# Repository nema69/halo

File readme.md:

# Light Module

## Anforderungen

- Ring mit OD = 50mm und ID = 15mm

- Strom max. 500 mA

- Nennspannung = 24V

## LEDs

#### HONGLITRONIC A2835W6H2-D01-8D2AB5

- LCSC: [C7423447]([A2835W6H2-D01-8D2AB5 HONGLITRONIC(Hongli Zhihui (HONGLITRONIC)) | Optoelectronics - LCSC Electronics](https://www.lcsc.com/product-detail/LED-Indication-Discrete_HONGLITRONIC-Hongli-Zhihui-HONGLITRONIC-A2835W6H2-D01-8D2AB5_C7423447.html))

- Package: SMD2835

- Farbe: Kaltweiß (6500K)

- 

## TODO:

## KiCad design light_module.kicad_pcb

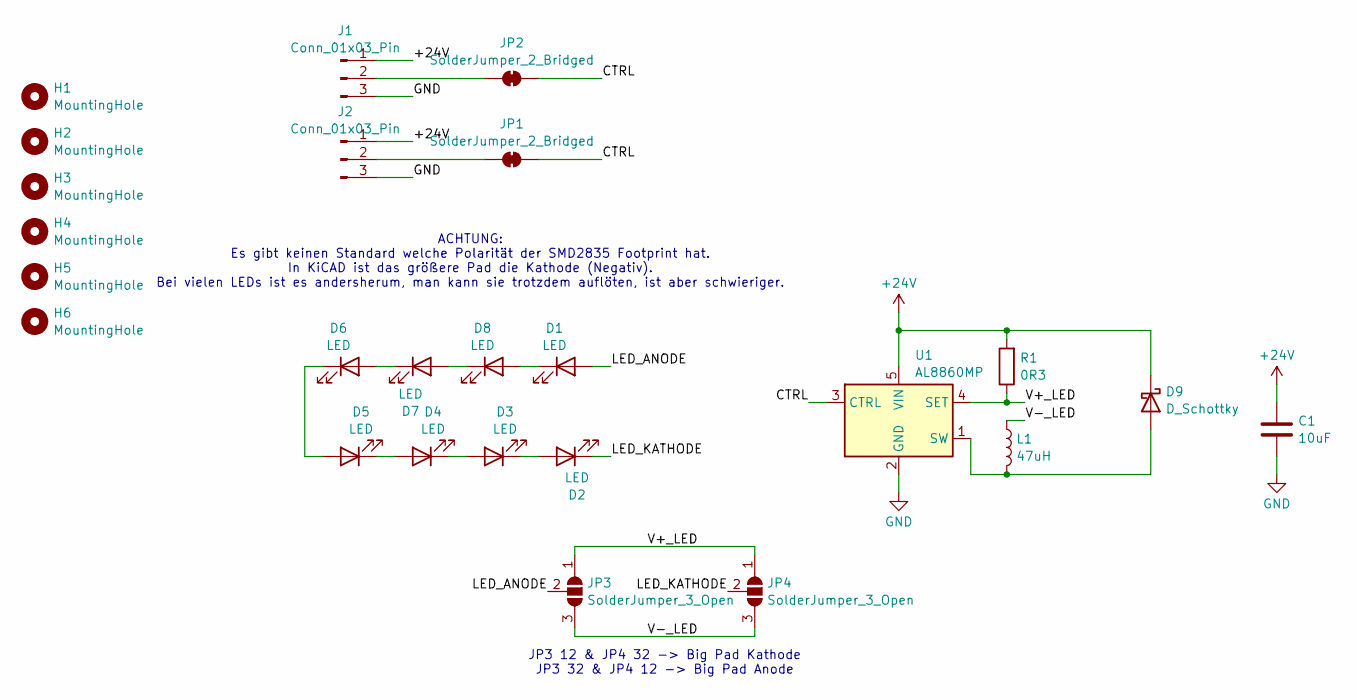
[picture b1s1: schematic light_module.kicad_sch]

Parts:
C1: 10uF; C_1206_3216Metric_Pad1.33x1.80mm_HandSolder; JLC PN C13585
D1, D2, D3, D4, D5, D6, D7, D8: LED; LED_PLCC_2835_Handsoldering; JLC PN C385302
D9: D_Schottky; D_SOD-123; JLC PN C78545
H1, H2, H3, H4, H5, H6: MountingHole; MountingHole_3.2mm_M3
J1, J2: Conn_01x03_Pin; JST_XH_B3B-XH-A_1x03_P2.50mm_Vertical
JP1, JP2: SolderJumper_2_Bridged; SolderJumper-2_P1.3mm_Bridged_RoundedPad1.0x1.5mm
JP3, JP4: SolderJumper_3_Open; SolderJumper-3_P1.3mm_Open_RoundedPad1.0x1.5mm_NumberLabels
L1: 47uH; L_Changjiang_FNR5020S; JLC PN C5363775
R1: 0R3; R_0805_2012Metric; JLC PN C247157
U1: AL8860MP; TSOT-23-5; JLC PN C155534

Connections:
+24V: C1.1, D9.1 (K), J1.1, J2.1, R1.2, U1.5 (VIN)
/CTRL: JP1.2 (B), JP2.2 (B), U1.3 (CTRL)
/LED_ANODE: D1.2 (A), JP3.2 (C)
/LED_KATHODE: D2.1 (K), JP4.2 (C)
/V+_LED: JP3.1 (A), JP4.1 (A), R1.1, U1.4 (SET)
/V-_LED: JP3.3 (B), JP4.3 (B), L1.1
GND: C1.2, J1.3, J2.3, U1.2 (GND)
unnamed: D1.1 (K), D8.2 (A)
unnamed: D2.2 (A), D3.1 (K)
unnamed: D3.2 (A), D4.1 (K)
unnamed: D4.2 (A), D5.1 (K)
unnamed: D5.2 (A), D6.1 (K)
unnamed: D6.2 (A), D7.1 (K)
unnamed: D7.2 (A), D8.1 (K)
unnamed: D9.2 (A), L1.2, U1.1 (SW)
unnamed: J1.2, JP2.1 (A)
unnamed: J2.2, JP1.1 (A)

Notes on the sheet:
JP3 12 & JP4 32 -> Big Pad Kathode JP3 32 & JP4 12 -> Big Pad Anode
ACHTUNG: Es gibt keinen Standard welche Polarität der SMD2835 Footprint hat. In KiCAD ist das größere Pad die Kathode (Negativ). Bei vielen LEDs ist es andersherum, man kann sie trotzdem auflöten, ist aber schwieriger.

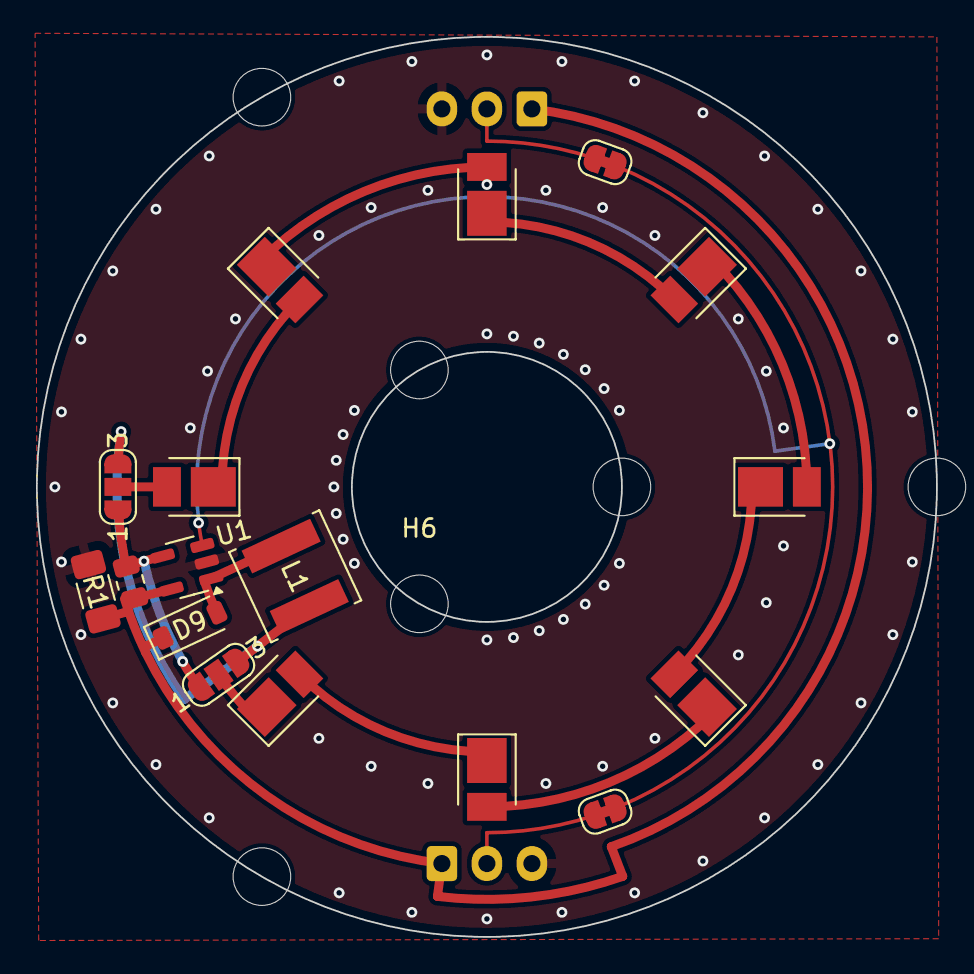
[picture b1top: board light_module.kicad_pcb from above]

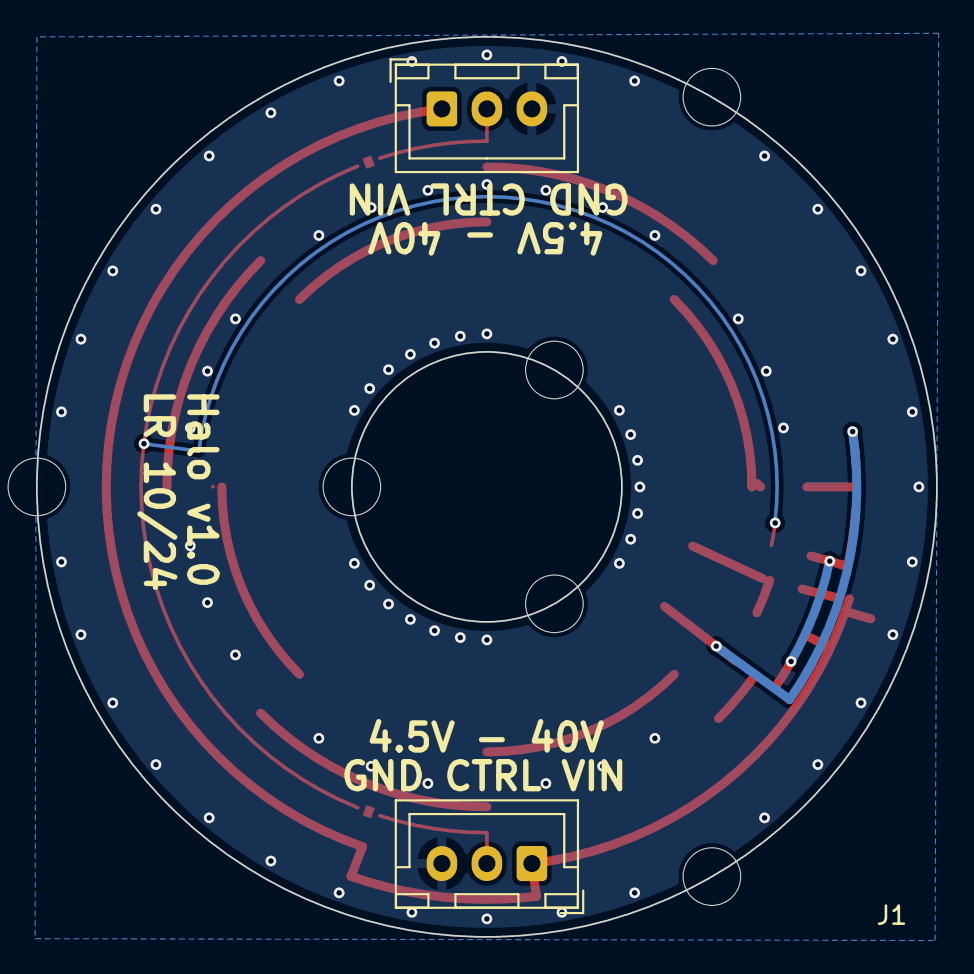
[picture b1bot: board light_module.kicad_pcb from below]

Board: 2 copper layers, 50.0 x 50.0 mm, 25 parts (2 on the bottom side), 17 nets.

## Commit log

2024-11-09 initial commit v1.0
2024-11-11 round
2024-11-11 added readme
